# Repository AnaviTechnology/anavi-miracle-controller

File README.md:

# ANAVI Miracle Controller

ANAVI Miracle Controller is an open source hardware development board for controlling 2 12V or 5V addressable LED strips. It features:

* ESP8266 WiFi microcontroller
* Terminals for 2 12V or 5V addressable LED strips (WS2811, WS2812, TM1804, etc.)
* Jumper to select 12V or 5V power input
* Dedicated slot for I2C OLED display
* Slots for up to 3 plug and play I2C sensors for temperature, barometric pressure, humidity and light
* UART (Universal asynchronous receiver/transmitter) pins for debugging

Open source software for ANAVI Miracle Controller written as an [Arduino sketch is also available at GitHub](https://github.com/AnaviTechnology/anavi-miracle-controller-sw).

# License

The project is released under the [Creative Commons Attribution-ShareAlike 4.0 International (CC BY-SA 4.0)](https://creativecommons.org/licenses/by-sa/4.0/).

Note: This is a human-readable summary of (and not a substitute for) the [license](https://creativecommons.org/licenses/by-sa/4.0/legalcode).

You are free to:

Share — copy and redistribute the material in any medium or format Adapt — remix, transform, and build upon the material for any purpose, even commercially. The licensor cannot revoke these freedoms as long as you follow the license terms. Under the following terms:

Attribution — You must give appropriate credit, provide a link to the license, and indicate if changes were made. You may do so in any reasonable manner, but not in any way that suggests the licensor endorses you or your use. ShareAlike — If you remix, transform, or build upon the material, you must distribute your contributions under the same license as the original. No additional restrictions — You may not apply legal terms or technological measures that legally restrict others from doing anything the license permits. Notices:

You do not have to comply with the license for elements of the material in the public domain or where your use is permitted by an applicable exception or limitation. No warranties are given. The license may not give you all of the permissions necessary for your intended use. For example, other rights such as publicity, privacy, or moral rights may limit how you use the material.

You will have to provide a link to the original creator of the project http://www.anavi.technology on any documentation or website.

Credit can be attributed through a link to the creator website: http://www.anavi.technology

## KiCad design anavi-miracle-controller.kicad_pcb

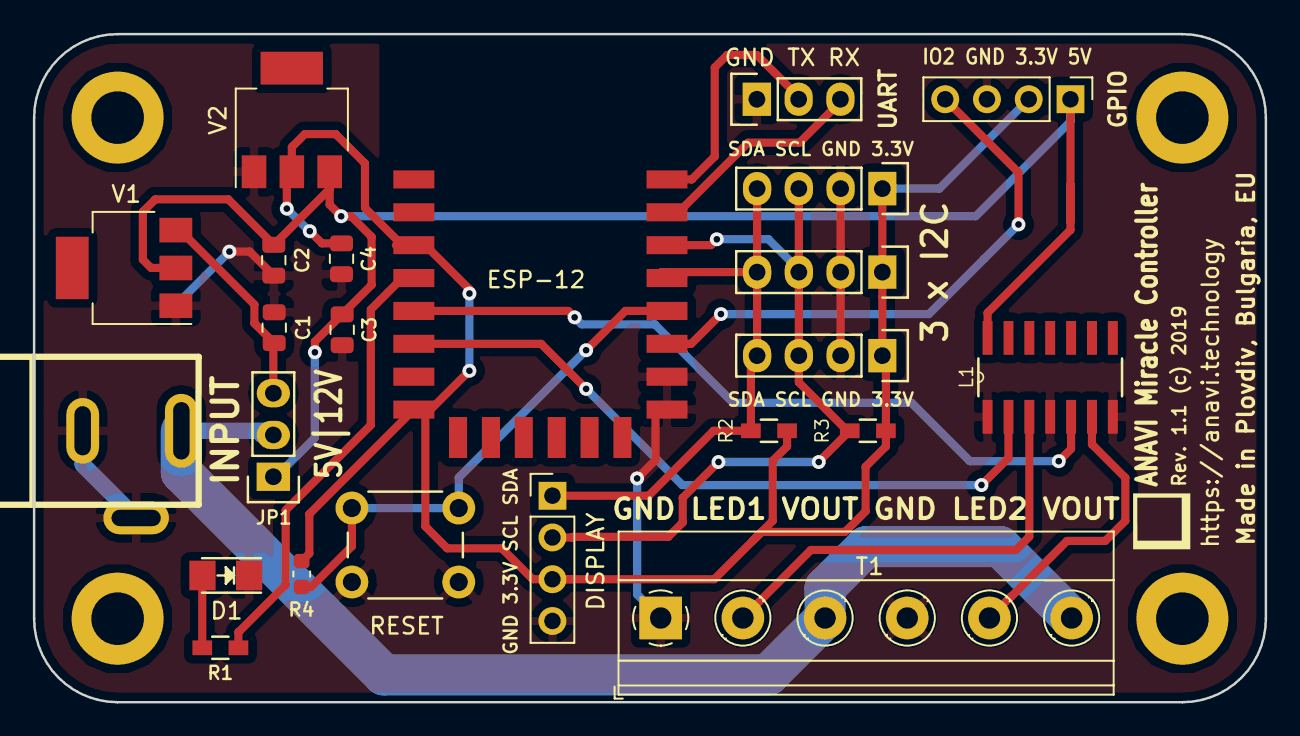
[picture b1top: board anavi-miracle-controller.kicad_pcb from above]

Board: 2 copper layers, 74.9 x 40.6 mm, 23 parts (0 on the bottom side), 17 nets.

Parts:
C1, C2, C3, C4: 10uF; C_0805_2012Metric
D1: LED; LED_1206
DISPLAY: Conn_01x04; PinHeader_1x04_P2.54mm_Vertical
ESP-12: ESP-12E; ESP-12E_SMD
GPIO: Conn_01x04; PinHeader_1x04_P2.54mm_Vertical
J1: INPUT; dc_socket
JP1: SolderJumper_3_Open; Pin_Header_Straight_1x03
L1: SN74AHCT125D; SOIC127P600X175-14N
P1: CONN_01X03; Pin_Header_Straight_1x03
R1: 68R; R_0603_HandSoldering
R2, R3: 4,7K; R_0603_HandSoldering
R4: 2K; R_0603_1608Metric
RESET: SW_DIP_x01; SW_PUSH_6mm_h4.3mm
T1: Screw_Terminal_01x06; TerminalBlock_Phoenix_MKDS-1,5-6_1x06_P5.00mm_Horizontal
U1, U2, U3: I2C_SENS_1; Pin_Header_Straight_1x04
V1: NCP1117ST50T3G; SOT-223
V2: NCP1117ST33T3G; SOT-223

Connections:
+3V3: C4.1, DISPLAY.3, ESP-12.3, ESP-12.8, GPIO.2, R2.1, R3.1, R4.2, U1.1, U2.1, U3.1, V2.2
+5V: C2.1, C3.1, GPIO.1, JP1.1, L1.14, V1.2, V2.3
+12V: C1.1, JP1.3, V1.3
/LED1: L1.3, T1.2
/LED2: L1.6, T1.5
GND: C1.2, C2.2, C3.2, C4.2, D1.1, DISPLAY.4, ESP-12.9, ESP-12.10, GPIO.3, J1.1, J1.2, L1.1, L1.4, L1.7, P1.1, RESET.1, T1.1, T1.4, U1.2, U2.2, U3.2, V1.1, V2.1
unnamed: D1.2, R1.2
unnamed: ESP-12.4, R1.1
unnamed: ESP-12.5, L1.5
unnamed: ESP-12.6, L1.2
unnamed: ESP-12.11, GPIO.4
unnamed: ESP-12.12, R4.1, RESET.2
unnamed: DISPLAY.1, ESP-12.13, R2.2, U1.4, U2.4, U3.4
unnamed: DISPLAY.2, ESP-12.14, R3.2, U1.3, U2.3, U3.3
unnamed: ESP-12.15, P1.3
unnamed: ESP-12.16, P1.2
unnamed: J1.3, JP1.2, T1.3, T1.6

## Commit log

2019-06-01 Intial release
2019-06-01 Update schematics and PCB design
    Major update to add SN74AHCT125D and to make the PCB design.
2019-06-01 anavi-miracle-controller.kicad_pcb: Fix outline
    Fix the outline to export properly gerber and drill files.
2019-06-01 anavi-miracle-controller.kicad_pcb: Labels
    Improve text labels and their positions.
2019-06-03 anavi-miracle-controller.kicad_pcb: Improvements
    Minor improvements of rev 1.0.
2019-06-09 Revision 1.1: Fix DC Jack
    Update the schedatics, fix the DC jack on the PCB.
2019-06-21 anavi-miracle-controller.kicad_pcb: Assembly
    Update assembly guidelines on the board.
2019-07-14 anavi-miracle-controller.pro: Minor updates
2019-07-14 README.md: Add details
    Add details for ANAVI Miracle Controller.
2019-07-14 README.md: Fix link
    Fix a broken link.

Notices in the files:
anavi-miracle-controller.kicad_pcb:
Rev. 1.1 (c) 2019
